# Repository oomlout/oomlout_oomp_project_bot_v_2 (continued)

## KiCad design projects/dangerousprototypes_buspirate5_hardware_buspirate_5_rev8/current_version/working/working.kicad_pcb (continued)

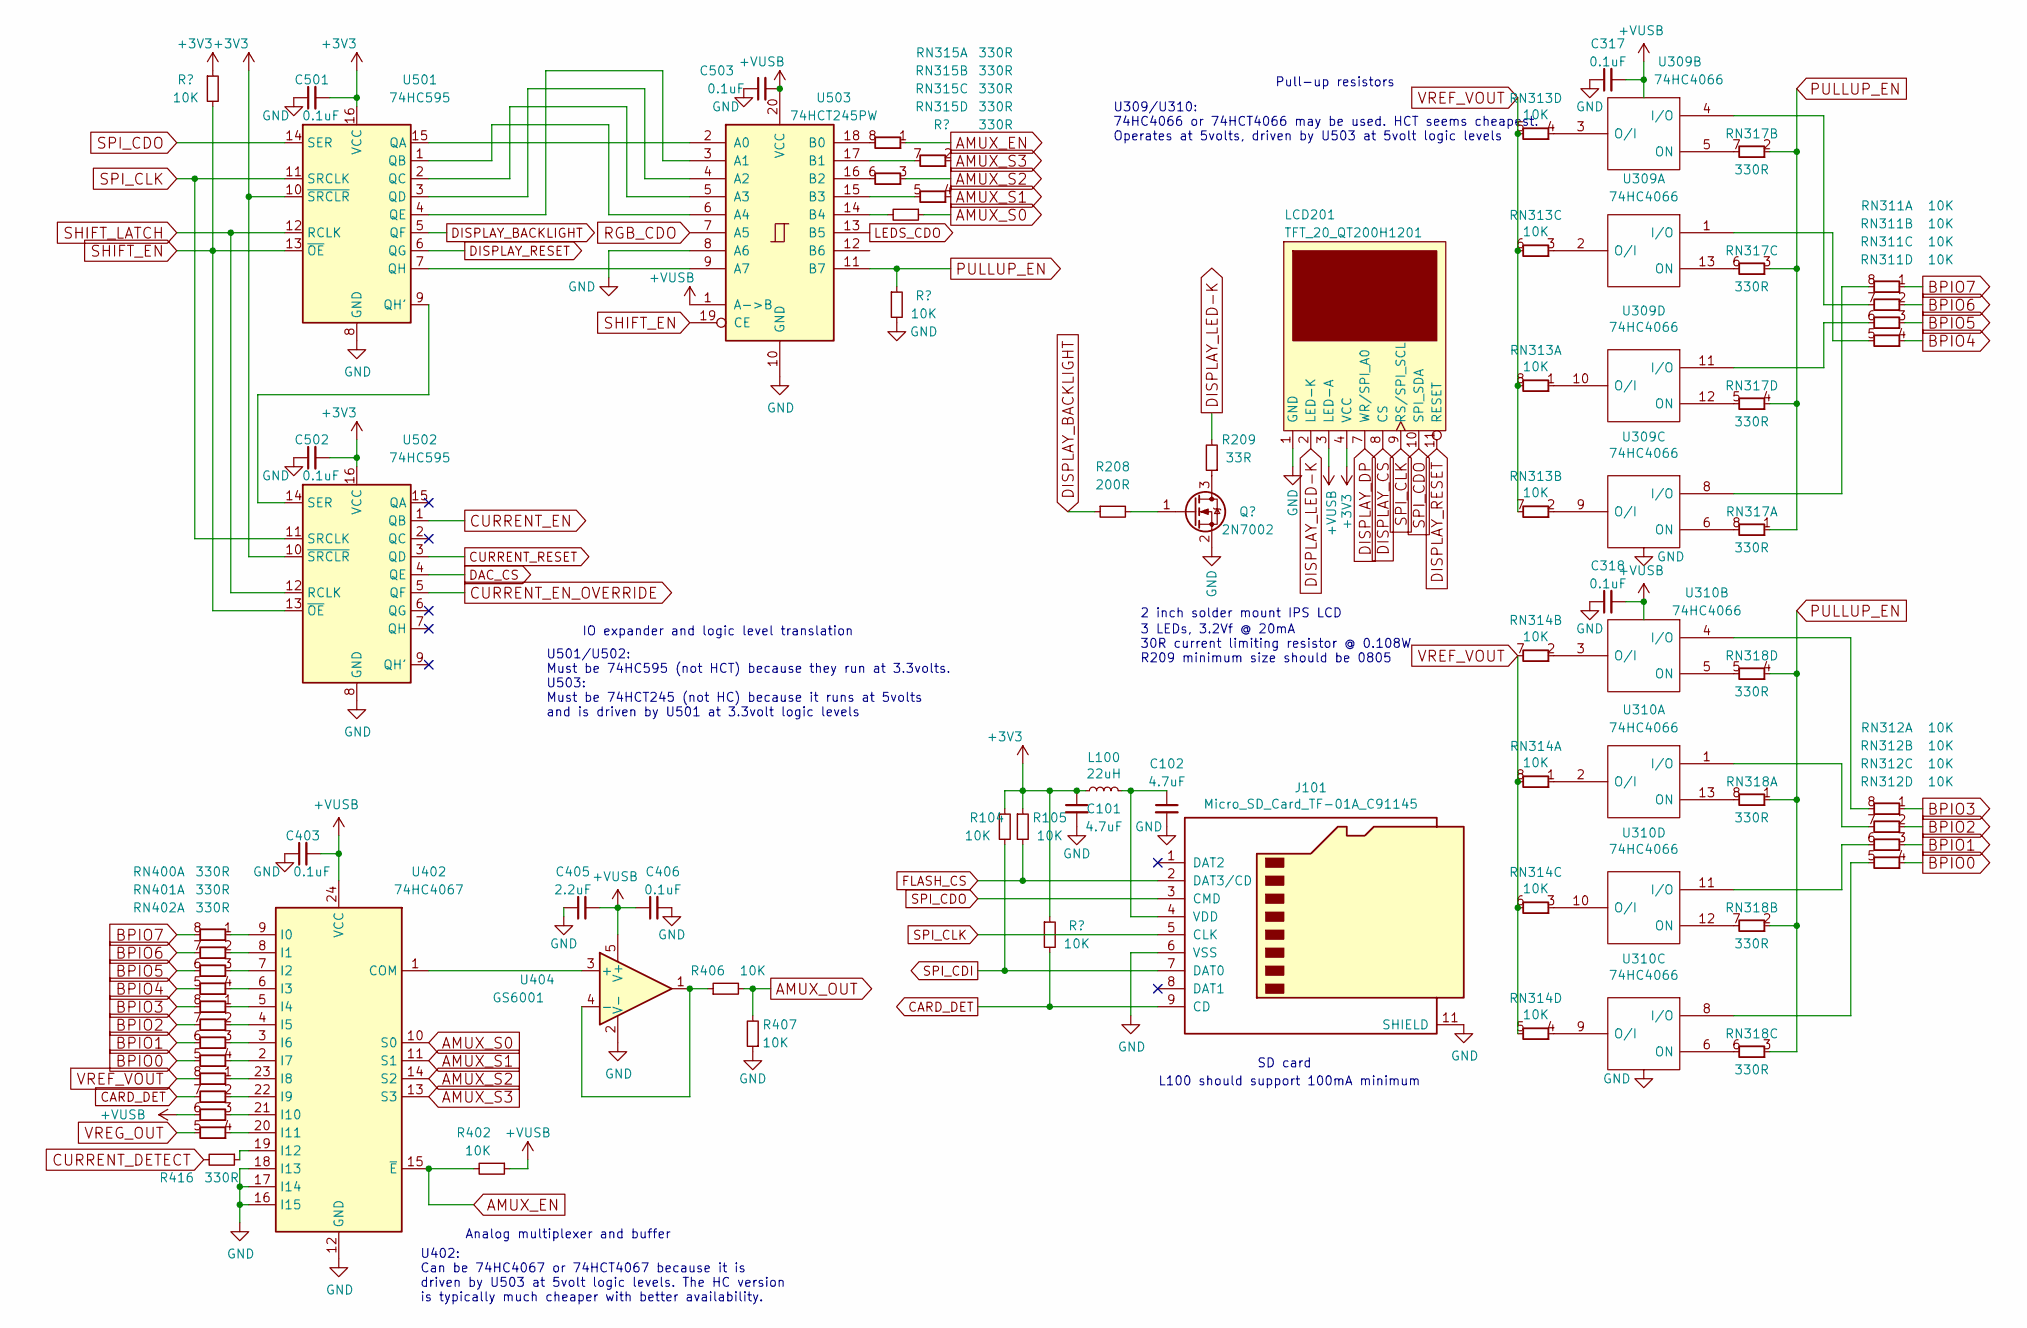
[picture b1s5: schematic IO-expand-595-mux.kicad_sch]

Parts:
C101, C102: 4.7uF; C_0402_1005Metric
C317, C318, C403, C406, C501, C502, C503: 0.1uF; C_0402_1005Metric
C405: 2.2uF; C_0402_1005Metric
J101: Micro_SD_Card_TF-01A_C91145; TF-01A_C91145
L100: 22uH; L_0603_1608Metric
LCD201: TFT_20_QT200H1201
Q202: 2N7002; SOT-23
R104, R105, R106, R312, R402, R406, R407, R501: 10K; R_0402_1005Metric
R208: 200R; R_0402_1005Metric
R209: 33R; R_0805_2012Metric
R316, R416: 330R; R_0402_1005Metric
RN311, RN312, RN313, RN314: 10K; R_Array_Convex_4x0402
RN315, RN317, RN318, RN400, RN401, RN402: 330R; R_Array_Convex_4x0402
U309, U310: 74HC4066; TSSOP-14_4.4x5mm_P0.65mm
U402: 74HC4067; TSSOP-24_4.4x7.8mm_P0.65mm
U404: GS6001; SOT-23-5
U501, U502: 74HC595; TSSOP-16_4.4x5mm_P0.65mm
U503: 74HCT245PW; TSSOP-20_4.4x6.5mm_P0.65mm

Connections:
+VUSB: C317.2, C318.2, C403.2, C405.2, C406.1, C503.2, LCD201.3 (LED-A), R402.1, RN402.6 (R1.8), U309.14 (Vdd), U310.14 (Vdd), U402.24 (VCC), U404.5 (V+), U503.1 (A->B), U503.20 (VCC); also elsewhere on the board
AMUX_EN: R402.2, RN315.1 (R1.1), U402.15 (~E)
AMUX_OUT: R406.2, R407.2; also elsewhere on the board
AMUX_S0: R316.1, U402.10 (S0)
AMUX_S1: RN315.4 (R1.1), U402.11 (S1)
AMUX_S2: RN315.3 (R1.1), U402.14 (S2)
AMUX_S3: RN315.2 (R1.1), U402.13 (S3)
BPIO0: RN312.4 (R1.1), RN401.5 (R1.8); also elsewhere on the board
BPIO1: RN312.3 (R1.1), RN401.6 (R1.8); also elsewhere on the board
BPIO2: RN312.2 (R1.1), RN401.7 (R1.8); also elsewhere on the board
BPIO3: RN312.1 (R1.1), RN401.8 (R1.8); also elsewhere on the board
BPIO4: RN311.4 (R1.1), RN400.5 (R1.8); also elsewhere on the board
BPIO5: RN311.3 (R1.1), RN400.6 (R1.8); also elsewhere on the board
BPIO6: RN311.2 (R1.1), RN400.7 (R1.8); also elsewhere on the board
BPIO7: RN311.1 (R1.1), RN400.8 (R1.8); also elsewhere on the board
CARD_DET: J101.9 (CD), R106.2, RN402.7 (R1.8)
CURRENT_DETECT: R416.2; also elsewhere on the board
CURRENT_EN: U502.1 (QB); also elsewhere on the board
CURRENT_EN_OVERRIDE: U502.5 (QF); also elsewhere on the board
CURRENT_RESET: U502.3 (QD); also elsewhere on the board
DAC_CS: U502.4 (QE)
DISPLAY_BACKLIGHT: R208.1, U501.5 (QF)
DISPLAY_CS: LCD201.8 (CS); also elsewhere on the board
DISPLAY_DP: LCD201.7 (WR/SPI_A0); also elsewhere on the board
DISPLAY_LED-K: LCD201.2 (LED-K), R209.2
DISPLAY_RESET: LCD201.11 (RESET), U501.6 (QG)
FLASH_CS: J101.2 (DAT3/CD), R105.2; also elsewhere on the board
GND: C101.2, C102.2, C317.1, C318.1, C403.1, C405.1, C406.2, C501.1, C502.1, C503.1, J101.6 (VSS), J101.11 (SHIELD), LCD201.1 (GND), LCD201.5 (GND), LCD201.6 (GND), LCD201.12 (GND), Q202.2 (S), R312.2, R407.1, U309.7 (Vss), U310.7 (Vss), U402.12 (GND), U402.16 (I15), U402.17 (I14), U402.18 (I13), U404.2 (V-), U501.8 (GND), U502.8 (GND), U503.8 (A6), U503.10 (GND); also elsewhere on the board
LEDS_CDO: U503.13 (B5); also elsewhere on the board
unnamed: C102.1, J101.4 (VDD), L100.2
unnamed: Q202.1 (G), R208.2
unnamed: Q202.3 (D), R209.1
unnamed: R316.2, U503.14 (B4)
unnamed: R406.1, U404.1, U404.4 (-)
unnamed: R416.1, U402.19 (I12)
unnamed: RN311.5 (R1.8), U309.1 (I/O)
unnamed: RN311.6 (R1.8), U309.11 (I/O)
unnamed: RN311.7 (R1.8), U309.4 (I/O)
unnamed: RN311.8 (R1.8), U309.8 (I/O)
unnamed: RN312.5 (R1.8), U310.8 (I/O)
unnamed: RN312.6 (R1.8), U310.11 (I/O)
unnamed: RN312.7 (R1.8), U310.1 (I/O)
unnamed: RN312.8 (R1.8), U310.4 (I/O)
unnamed: RN313.1 (R1.1), U309.10 (O/I)
unnamed: RN313.2 (R1.1), U309.9 (O/I)
unnamed: RN313.3 (R1.1), U309.2 (O/I)
unnamed: RN313.4 (R1.1), U309.3 (O/I)
unnamed: RN314.1 (R1.1), U310.2 (O/I)
unnamed: RN314.2 (R1.1), U310.3 (O/I)
unnamed: RN314.3 (R1.1), U310.10 (O/I)
unnamed: RN314.4 (R1.1), U310.9 (O/I)
unnamed: RN315.5 (R1.8), U503.15 (B3)
unnamed: RN315.6 (R1.8), U503.16 (B2)
unnamed: RN315.7 (R1.8), U503.17 (B1)
unnamed: RN315.8 (R1.8), U503.18 (B0)
unnamed: RN317.5 (R1.8), U309.12 (ON)
unnamed: RN317.6 (R1.8), U309.13 (ON)
unnamed: RN317.7 (R1.8), U309.5 (ON)
unnamed: RN317.8 (R1.8), U309.6 (ON)
unnamed: RN318.5 (R1.8), U310.5 (ON)
unnamed: RN318.6 (R1.8), U310.6 (ON)
unnamed: RN318.7 (R1.8), U310.12 (ON)
unnamed: RN318.8 (R1.8), U310.13 (ON)
unnamed: RN400.1 (R1.1), U402.9 (I0)
unnamed: RN400.2 (R1.1), U402.8 (I1)
unnamed: RN400.3 (R1.1), U402.7 (I2)
unnamed: RN400.4 (R1.1), U402.6 (I3)
unnamed: RN401.1 (R1.1), U402.5 (I4)
unnamed: RN401.2 (R1.1), U402.4 (I5)
unnamed: RN401.3 (R1.1), U402.3 (I6)
unnamed: RN401.4 (R1.1), U402.2 (I7)
unnamed: RN402.1 (R1.1), U402.23 (I8)
unnamed: RN402.2 (R1.1), U402.22 (I9)
unnamed: RN402.3 (R1.1), U402.21 (I10)
unnamed: RN402.4 (R1.1), U402.20 (I11)
unnamed: U402.1 (COM), U404.3 (+)
unnamed: U501.1 (QB), U503.6 (A4)
unnamed: U501.2 (QC), U503.5 (A3)
unnamed: U501.3 (QD), U503.4 (A2)
unnamed: U501.4 (QE), U503.3 (A1)
unnamed: U501.7 (QH), U503.9 (A7)
unnamed: U501.9 (QH'), U502.14 (SER)
unnamed: U501.15 (QA), U503.2 (A0)
PULLUP_EN: R312.1, RN317.1 (R1.1), RN317.2 (R1.1), RN317.3 (R1.1), RN317.4 (R1.1), RN318.1 (R1.1), RN318.2 (R1.1), RN318.3 (R1.1), RN318.4 (R1.1), U503.11 (B7)
RGB_CDO: U503.7 (A5); also elsewhere on the board
SHIFT_EN: R501.2, U501.13 (~OE), U502.13 (~OE), U503.19 (CE); also elsewhere on the board
SHIFT_LATCH: U501.12 (RCLK), U502.12 (RCLK); also elsewhere on the board
SPI_CDI: J101.7 (DAT0), R104.2; also elsewhere on the board
SPI_CDO: J101.3 (CMD), LCD201.10 (SPI_SDA), U501.14 (SER); also elsewhere on the board
SPI_CLK: J101.5 (CLK), LCD201.9 (RS/SPI_SCL), U501.11 (SRCLK), U502.11 (SRCLK); also elsewhere on the board
VREF_VOUT: RN313.5 (R1.8), RN313.6 (R1.8), RN313.7 (R1.8), RN313.8 (R1.8), RN314.5 (R1.8), RN314.6 (R1.8), RN314.7 (R1.8), RN314.8 (R1.8), RN402.8 (R1.8); also elsewhere on the board
VREG_OUT: RN402.5 (R1.8); also elsewhere on the board

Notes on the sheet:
3 LEDs, 3.2Vf @ 20mA 30R current limiting resistor @ 0.108W R209 minimum size should be 0805
2 inch solder mount IPS LCD
U402: Can be 74HC4067 or 74HCT4067 because it is driven by U503 at 5volt logic levels. The HC version is typically much cheaper with better availability.
SD card
Analog multiplexer and buffer
U501/U502: Must be 74HC595 (not HCT) because they run at 3.3volts. U503: Must be 74HCT245 (not HC) because it runs at 5volts and is driven by U501 at 3.3volt logic levels
U309/U310: 74HC4066 or 74HCT4066 may be used. HCT seems cheapest. Operates at 5volts, driven by U503 at 5volt logic levels
L100 should support 100mA minimum
IO expander and logic level translation
Pull-up resistors

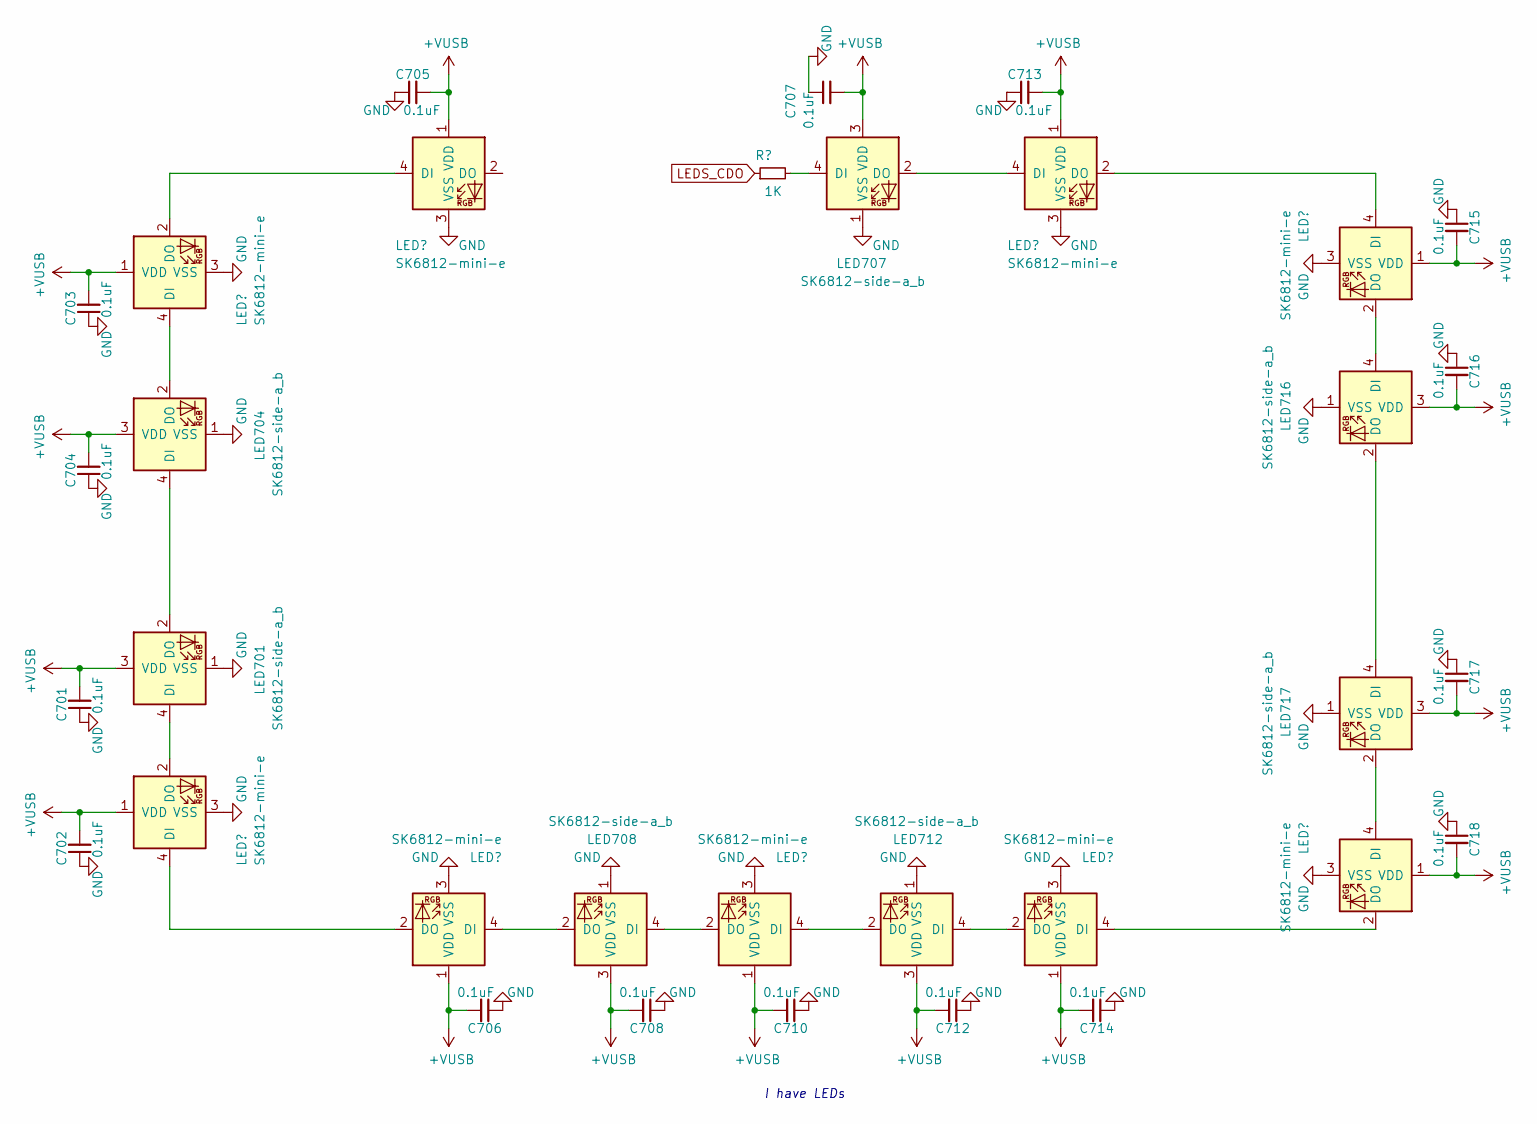
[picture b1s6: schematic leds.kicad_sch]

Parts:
C701, C702, C703, C704, C705, C706, C707, C708, C710, C712, C713, C714, C715, C716, C717, C718: 0.1uF; C_0402_1005Metric
LED701, LED704, LED707, LED708, LED712, LED716, LED717: SK6812-side-a_b
LED702, LED703, LED705, LED706, LED710, LED713, LED714, LED715, LED718: SK6812-mini-e
R502: 1K; R_0402_1005Metric

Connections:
+VUSB: C701.2, C702.2, C703.2, C704.2, C705.2, C706.2, C707.2, C708.2, C710.2, C712.2, C713.2, C714.2, C715.2, C716.2, C717.2, C718.2, LED701.3 (VDD), LED702.1 (VDD), LED703.1 (VDD), LED704.3 (VDD), LED705.1 (VDD), LED706.1 (VDD), LED707.3 (VDD), LED708.3 (VDD), LED710.1 (VDD), LED712.3 (VDD), LED713.1 (VDD), LED714.1 (VDD), LED715.1 (VDD), LED716.3 (VDD), LED717.3 (VDD), LED718.1 (VDD); also elsewhere on the board
GND: C701.1, C702.1, C703.1, C704.1, C705.1, C706.1, C707.1, C708.1, C710.1, C712.1, C713.1, C714.1, C715.1, C716.1, C717.1, C718.1, LED701.1 (VSS), LED702.3 (VSS), LED703.3 (VSS), LED704.1 (VSS), LED705.3 (VSS), LED706.3 (VSS), LED707.1 (VSS), LED708.1 (VSS), LED710.3 (VSS), LED712.1 (VSS), LED713.3 (VSS), LED714.3 (VSS), LED715.3 (VSS), LED716.1 (VSS), LED717.1 (VSS), LED718.3 (VSS); also elsewhere on the board
LEDS_CDO: R502.1; also elsewhere on the board
unnamed: LED701.2 (DO), LED704.4 (DI)
unnamed: LED701.4 (DI), LED702.2 (DO)
unnamed: LED702.4 (DI), LED706.2 (DO)
unnamed: LED703.2 (DO), LED705.4 (DI)
unnamed: LED703.4 (DI), LED704.2 (DO)
unnamed: LED706.4 (DI), LED708.2 (DO)
unnamed: LED707.2 (DO), LED713.4 (DI)
unnamed: LED707.4 (DI), R502.2
unnamed: LED708.4 (DI), LED710.2 (DO)
unnamed: LED710.4 (DI), LED712.2 (DO)
unnamed: LED712.4 (DI), LED714.2 (DO)
unnamed: LED713.2 (DO), LED715.4 (DI)
unnamed: LED714.4 (DI), LED718.2 (DO)
unnamed: LED715.2 (DO), LED716.4 (DI)
unnamed: LED716.2 (DO), LED717.4 (DI)
unnamed: LED717.2 (DO), LED718.4 (DI)

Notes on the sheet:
I have LEDs

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
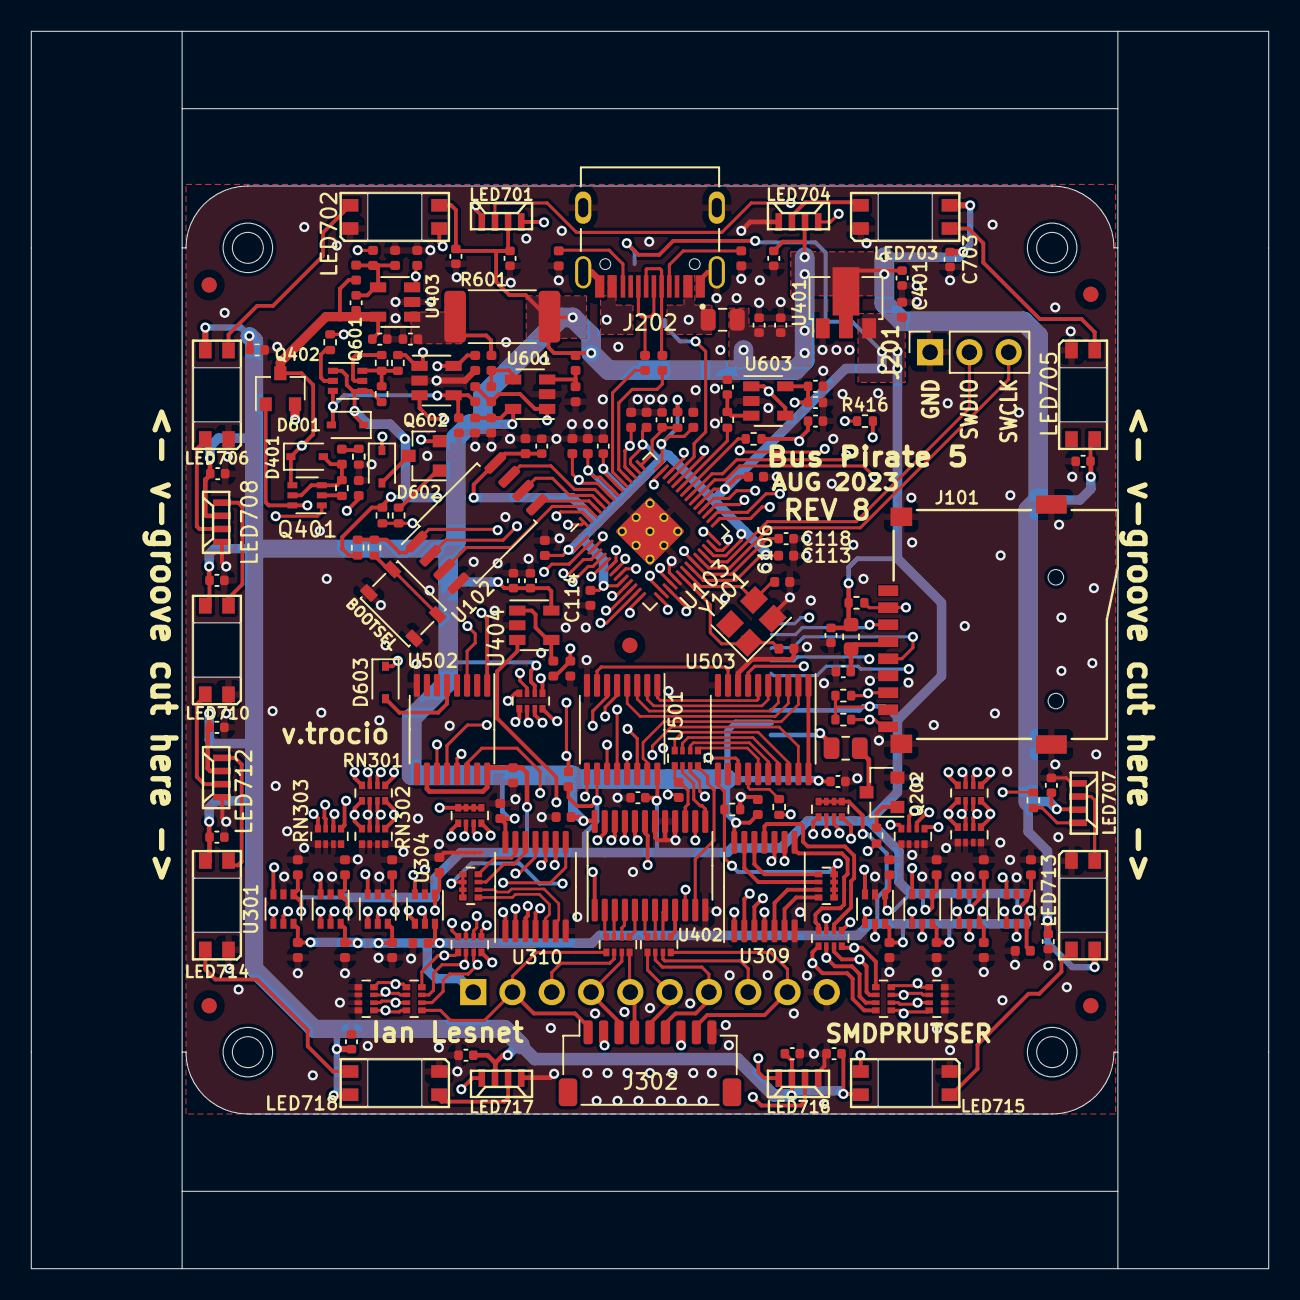
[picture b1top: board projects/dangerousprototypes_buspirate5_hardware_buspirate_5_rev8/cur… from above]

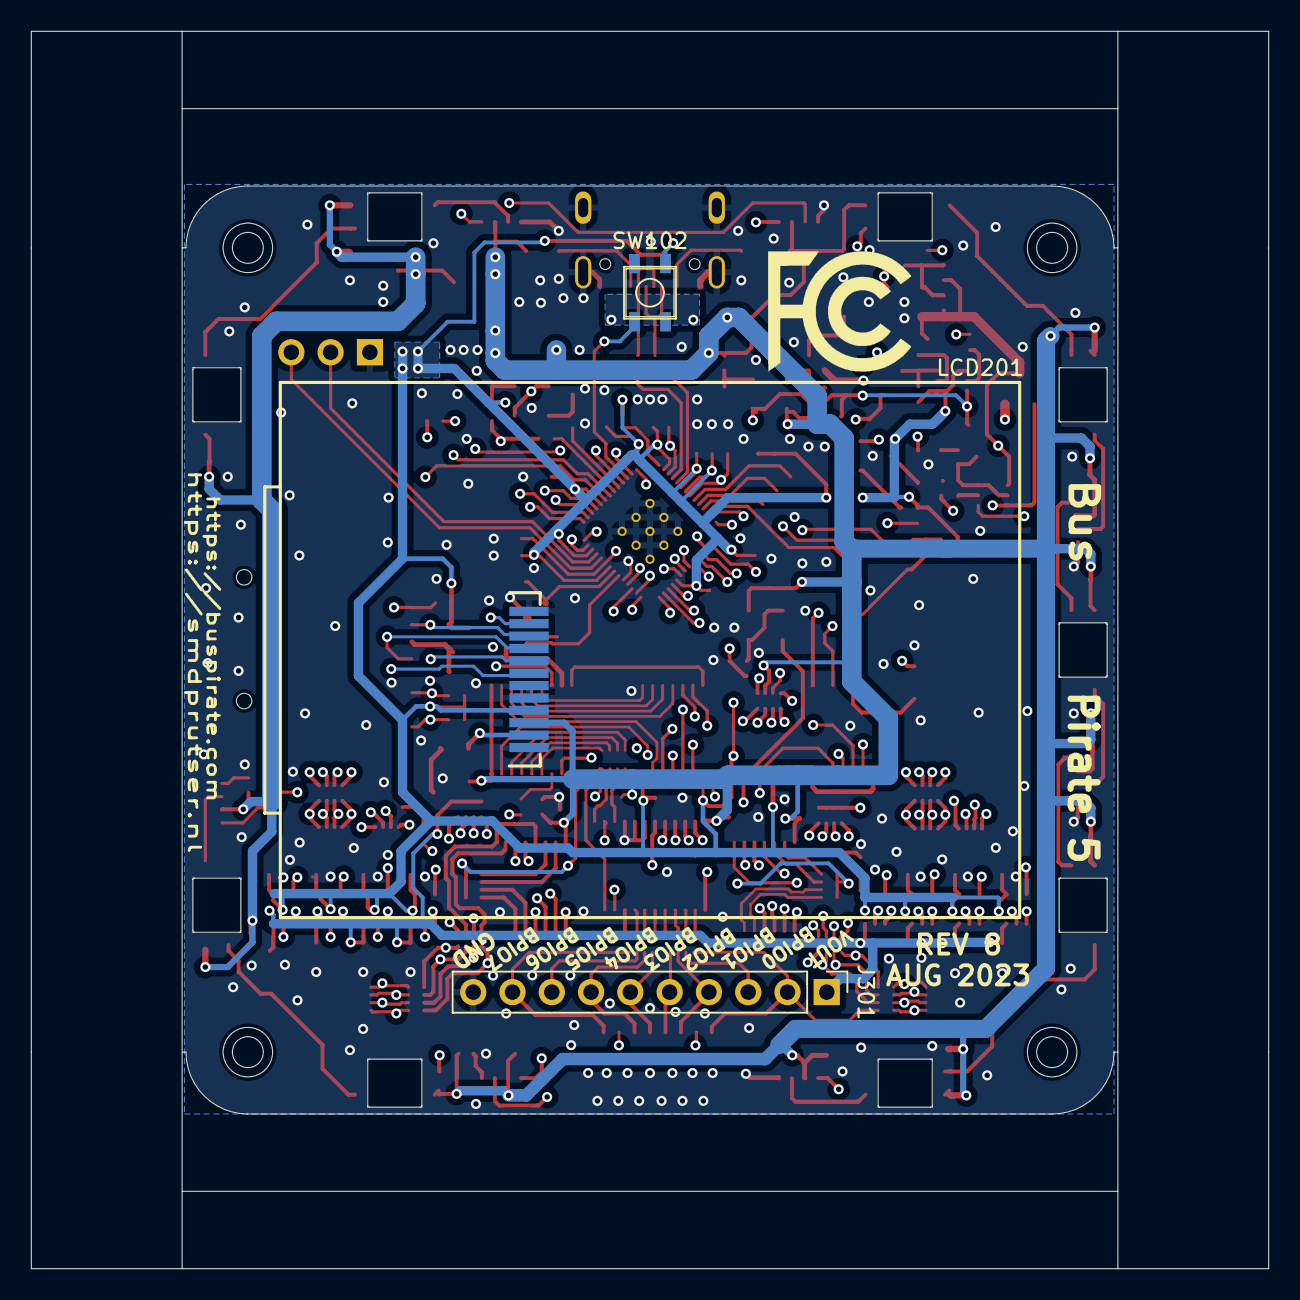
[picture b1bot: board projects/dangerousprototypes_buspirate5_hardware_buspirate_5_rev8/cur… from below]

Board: 4 copper layers, 80.0 x 80.0 mm, 203 parts (4 on the bottom side), 182 nets.

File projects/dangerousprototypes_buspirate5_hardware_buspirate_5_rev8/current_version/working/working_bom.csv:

"Id";"Designator";"Footprint";"Quantity";"Designation";"Supplier and ref";
1;"LED702,LED715,LED714,LED703,LED705,LED718,LED706,LED710,LED713";"SK6812-mini-e";9;"SK6812-mini-e";;;
2;"C402,C101,C202,C201,C401,C102,C404,C407";"C_0402_1005Metric";8;"4.7uF";;;
3;"C313,C308,C315,C304,C403,C314,C309,C112,C114,C110,C111,C113,C103,C118,C705,C708,C704,C706,C710,C712,C703,C701,C117,C501,C116,C715,C714,C716,C717,C718,C318,C502,C713,C406,C115,C707,C602,C605,C702,C311,C312,C503,C306,C307,C301,C302,C305,C303,C316,C317,C310,C414,C415,C416";"C_0402_1005Metric";54;"0.1uF";;;
4;"C107,C108,C109,C104,C405,C601,C413";"C_0402_1005Metric";7;"2.2uF";;;
5;"C106,C105";"C_0402_1005Metric";2;"15pF";;;
6;"U301,U304,U305,U307,U306,U303,U302,U308";"SOT-363_SC-70-6";8;"SN74LVC1T45DCK";;;
7;"R203,R202";"R_0402_1005Metric";2;"22R";;;
8;"R204,R201";"R_0402_1005Metric";2;"5.1K";;;
9;"L201";"L_0805_2012Metric";1;"1.5A";;;
10;"R407,R501,R402,R406,R104,R105,R410,R611,R609,R606,R610,R613,R106,R312,R414,R415";"R_0402_1005Metric";16;"10K";;;
11;"R103,R608,R612,R208";"R_0402_1005Metric";4;"200R";;;
12;"U103";"RP2040-QFN-56";1;"RP2040";;;
13;"U501,U502";"TSSOP-16_4.4x5mm_P0.65mm";2;"74HC595";;;
14;"RN302,RN307,RN304,RN310";"R_Array_Convex_4x0402";4;"1M";;;
15;"R209";"R_0805_2012Metric";1;"33R";;;
16;"U102";"SOP-8_5.28x5.23mm_P1.27mm";1;"W25Q128JVSIQ";;;
17;"U310,U309";"TSSOP-14_4.4x5mm_P0.65mm";2;"74HC4066";;;
18;"R101,R602,R603,R502";"R_0402_1005Metric";4;"1K";;;
19;"FID1,FID2,FID4,FID5,FID3";"Fiducial_1mm_Mask2mm";5;"Fiducial";;;
20;"J201";"PinSocket_1x03_P2.54mm_Vertical";1;"Conn_01x03";;;
21;"R102";"R_0402_1005Metric";1;"DNF";;;
22;"J302";"JST_SH_SM09B-SRSS-TB_1x09-1MP_P1.00mm_Horizontal";1;"Conn_01x09";;;
23;"U503";"TSSOP-20_4.4x6.5mm_P0.65mm";1;"74HCT245PW";;;
24;"Y101";"Crystal_SMD_3225-4Pin_3.2x2.5mm";1;"12Mhz";;;
25;"Q202";"SOT-23";1;"2N7002";;;
26;"L100";"L_0603_1608Metric";1;"22uH";;;
27;"J101";"TF-01A_C91145";1;"Micro_SD_Card_TF-01A_C91145";;;
28;"SW101";"SW_SPST_PTS810";1;"SW_SPST";;;
29;"D601,D401,D603,D602";"D_SOD-323";4;"1N4148WS";;;
30;"R405,R409,R408,R605,R604";"R_0402_1005Metric";5;"33K";;;
31;"R412,R401";"R_0402_1005Metric";2;"100K";;;
32;"R403";"R_0402_1005Metric";1;"102K";;;
33;"U601,U404,U603";"SOT-23-5";3;"GS6001";;;
34;"R601";"R_2512_6332Metric_Pad1.40x3.35mm_HandSolder";1;"0R2";;;
35;"C603";"C_0402_1005Metric";1;"DNF";;;
36;"U602";"SOT-23-5";1;"RS8901XF";;;
37;"Q402,Q602";"SOT-23";2;"WST3423";;;
38;"U403";"SOT-23-5";1;"AP2127";;;
39;"Q601";"SOT-363_SC-70-6";1;"MMDT3906";;;
40;"Q401";"SOT-363_SC-70-6";1;"BCM857";;;
41;"RN309,RN301,RN306,RN315,RN318,RN317,RN305,RN400,RN401,RN402";"R_Array_Convex_4x0402";10;"330R";;;
42;"U402";"TSSOP-24_4.4x7.8mm_P0.65mm";1;"74HC4067";;;
43;"RN303,RN308";"R_Array_Convex_4x0402";2;"100K";;;
44;"J202";"HRO_TYPE-C-31-M-12";1;"TYPE-C-31-M-12";;;
45;"RN313,RN314,RN312,RN311";"R_Array_Convex_4x0402";4;"10K";;;
46;"LED707,LED716,LED717,LED712,LED708,LED701,LED704";"SK6812-side-a_b";7;"SK6812-side-a_b";;;
47;"R316,R416";"R_0402_1005Metric";2;"330R";;;
48;"U401";"SOT-89-3";1;"ME6211A33PG-N";;;
49;"C408";"C_0402_1005Metric";1;"120pF";;;
50;"R404";"R_0402_1005Metric";1;"133K";;;
51;"J301";"PinHeader_1x10_P2.54mm_Vertical";1;"Conn_01x10";;;
52;"SW102";"GT-TC026X-HXXX-LX";1;"4P_button_sw";;;
53;"LCD201";"TFT_20_QT200H1201";1;"TFT_20_QT200H1201";;;
54;"logo1";"logo_fcc";1;"fcc_logo";;;

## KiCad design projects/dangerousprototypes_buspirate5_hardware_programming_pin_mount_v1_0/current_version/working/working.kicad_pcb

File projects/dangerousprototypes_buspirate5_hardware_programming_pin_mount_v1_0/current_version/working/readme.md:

# buspirate5_hardware
 
## summary 
* id: dangerousprototypes_buspirate5_hardware_programming_pin_mount_v1_0
* user: dangerousprototypes
* name: buspirate5_hardware
* board: programming_pin_mount_v1_0
* repo: https://github.com/DangerousPrototypes/BusPirate5-hardware
* src_file_repo_kicad_pcb: debug-station/programming_pin_mount.v1.0.kicad_pcb
* src_file_repo_kicad_pcb_link: https://github.com/DangerousPrototypes/BusPirate5-hardware/tree/main/debug-station/programming_pin_mount.v1.0.kicad_pcb

* src_file_repo_sch: debug-station/programming_pin_mount.v1.0.sch
* src_file_repo_sch_link: https://github.com/DangerousPrototypes/BusPirate5-hardware/tree/main/debug-station/programming_pin_mount.v1.0.sch
* full details link: https://github.com/oomlout/oomlout_oomp_project_bot_v_2/tree/main/projects/dangerousprototypes_buspirate5_hardware_programming_pin_mount_v1_0/current_version/working  

## schematic  
  
[schematic (pdf)](working_schematic.pdf) 

## pcb  

[board (pdf)](working.pdf)  

## working_bom
| Id | Designator | Footprint | Quantity | Designation | Supplier and ref |  | None | 
| --- | --- | --- | --- | --- | --- | --- | --- | 
| 1 | H1,H2,H3 | PinHeader_1x01_P1.00mm_Vertical | 3 | MountingHole_Pad |  |  | [''] | 
| 2 | J1 | PinHeader_1x03_P2.54mm_Horizontal | 1 | Conn_01x03 |  |  | [''] | 

## bom_schematic
| Ref | Qnty | Value | Cmp name | Footprint | Description | Vendor | DNP | 
| --- | --- | --- | --- | --- | --- | --- | --- | 
| H1, H2, H3 | 3 | MountingHole_Pad | MountingHole_Pad | Connector_PinHeader_1.00mm:PinHeader_1x01_P1.00mm_Vertical | Mounting Hole with connection |  |  | 
| H4, H5 | 2 | MountingHole | MountingHole | MountingHole:MountingHole_3.2mm_M3 | Mounting Hole without connection |  |  | 
| J1 | 1 | Conn_01x03 | Conn_01x03 | Connector_PinHeader_2.54mm:PinHeader_1x03_P2.54mm_Horizontal | Generic connector, single row, 01x03, script generated (kicad-library-utils/schlib/autogen/connector/) |  |  |

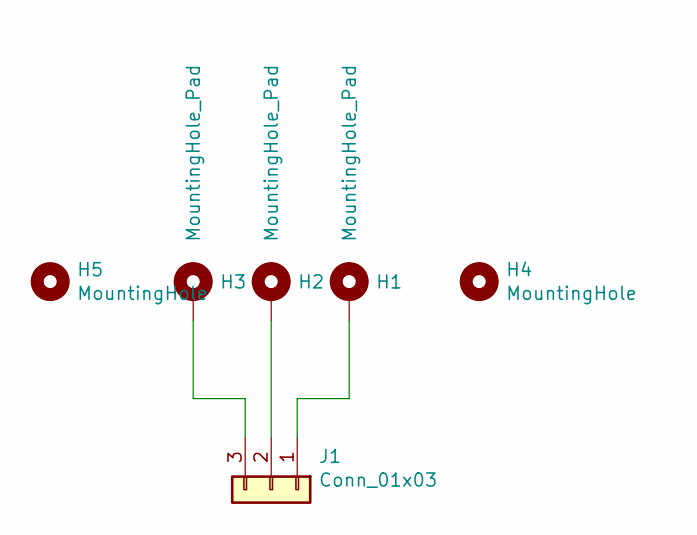
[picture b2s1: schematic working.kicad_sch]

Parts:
H1, H2, H3: MountingHole_Pad; PinHeader_1x01_P1.00mm_Vertical
H4, H5: MountingHole; MountingHole_3.2mm_M3
J1: Conn_01x03; PinHeader_1x03_P2.54mm_Horizontal

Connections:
unnamed: H1.1, J1.1
unnamed: H2.1, J1.2
unnamed: H3.1, J1.3

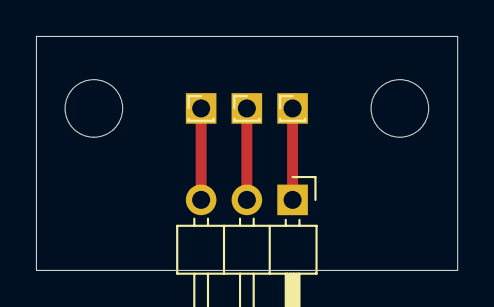
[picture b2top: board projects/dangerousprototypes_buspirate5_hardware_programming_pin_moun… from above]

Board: 2 copper layers, 23.4 x 13.0 mm, 6 parts (0 on the bottom side), 3 nets.

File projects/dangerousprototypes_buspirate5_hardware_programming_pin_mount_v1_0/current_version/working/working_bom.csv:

"Id";"Designator";"Footprint";"Quantity";"Designation";"Supplier and ref";
1;"H1,H2,H3";"PinHeader_1x01_P1.00mm_Vertical";3;"MountingHole_Pad";;;
2;"J1";"PinHeader_1x03_P2.54mm_Horizontal";1;"Conn_01x03";;;

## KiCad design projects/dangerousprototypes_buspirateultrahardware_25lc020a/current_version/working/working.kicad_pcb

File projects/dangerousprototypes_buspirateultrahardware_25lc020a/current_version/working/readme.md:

# buspirateultrahardware
 
## summary 
* id: dangerousprototypes_buspirateultrahardware_25lc020a
* user: dangerousprototypes
* name: buspirateultrahardware
* board: 25lc020a
* repo: https://github.com/DangerousPrototypes/BusPirateUltraHardware

* src_file_repo_sch: 
* src_file_repo_sch_link: https://github.com/DangerousPrototypes/BusPirateUltraHardware/tree/master/
* full details link: https://github.com/oomlout/oomlout_oomp_project_bot_v_2/tree/main/projects/dangerousprototypes_buspirateultrahardware_25lc020a/current_version/working  

## schematic  
  
[schematic (pdf)](working_schematic.pdf) 

## pcb  

[board (pdf)](working.pdf)  

## working_bom
| Id | Designator | Footprint | Quantity | Designation | Supplier and ref |  | None | 
| --- | --- | --- | --- | --- | --- | --- | --- | 
| 1 | R3,R2,R1 | R603 | 3 |  |  |  | [''] | 
| 2 | J1 | M1X10_FEMALE_RIGHT_ANGLED_PTH | 1 | CON_HEADER_1X10-RIGHT_ANGLED_PTH |  |  | [''] | 
| 3 | LED1 | LED-805 | 1 |  |  |  | [''] | 
| 4 | @HOLE0,@HOLE1 |  | 2 |  |  |  | [''] | 
| 5 | C1 | C603 | 1 |  |  |  | [''] | 
| 6 | J2 | M1X10 | 1 | CON_HEADER_1X10-PTH |  |  | [''] | 
| 7 | IC1 | SOIC127P600X175-8N | 1 | 25LC020A |  |  | [''] | 

## bom_schematic
| Ref | Qnty | Value | Cmp name | Footprint | Description | Vendor | DNP | 
| --- | --- | --- | --- | --- | --- | --- | --- | 
| C1 | 1 | CAPACITOR_NPOL-0603 | CAPACITOR_NPOL-0603 | working:C603 |  |  |  | 
| IC1 | 1 | 25LC020A-I_SN | 25LC020A-I_SN | working:SOIC127P600X175-8N |  |  |  | 
| J1 | 1 | CON_HEADER_1X10-RIGHT_ANGLED_PTH | CON_HEADER_1X10-RIGHT_ANGLED_PTH | working:M1X10_FEMALE_RIGHT_ANGLED_PTH |  |  |  | 
| J2 | 1 | CON_HEADER_1X10-PTH | CON_HEADER_1X10-PTH | working:M1X10 |  |  |  | 
| LED1 | 1 | LED-0805 | LED-0805 | working:LED-805 |  |  |  | 
| R1, R2, R3 | 3 | RESISTOR-0603 | RESISTOR-0603 | working:R603 |  |  |  |

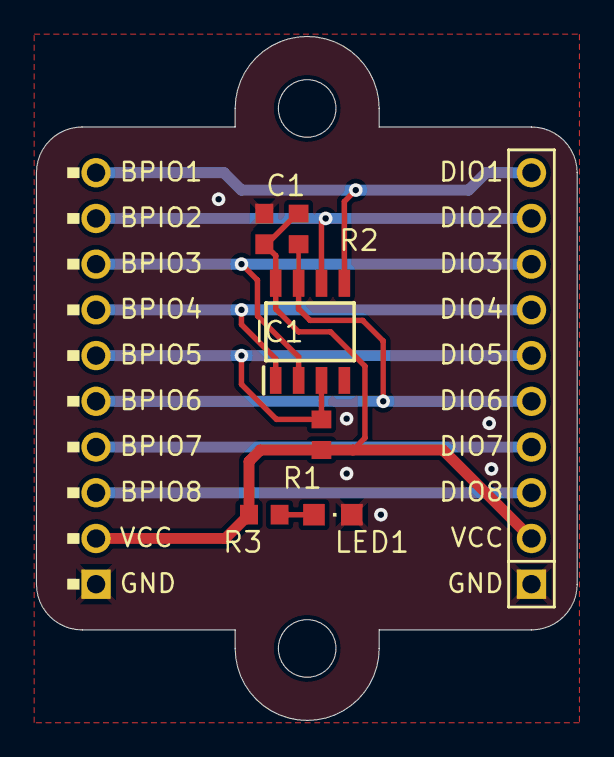
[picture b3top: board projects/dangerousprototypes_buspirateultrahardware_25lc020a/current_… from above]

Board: 2 copper layers, 30.0 x 38.0 mm, 10 parts (0 on the bottom side), 11 nets.

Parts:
@HOLE0, @HOLE1: (no value)
C1: C603
IC1: 25LC020A; SOIC127P600X175-8N
J1: CON_HEADER_1X10-RIGHT_ANGLED_PTH; M1X10_FEMALE_RIGHT_ANGLED_PTH
J2: CON_HEADER_1X10-PTH; M1X10
LED1: LED-805
R1, R2, R3: R603

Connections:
DIO1: IC1.5, J1.10, J2.10
DIO2: IC1.6, J1.9, J2.9
DIO3: IC1.2, J1.8, J2.8
DIO4: IC1.1, J1.7, J2.7
DIO5: IC1.3, J1.6, J2.6, R1.1
DIO6: IC1.7, J1.5, J2.5, R2.1
DIO7: J1.4, J2.4
DIO8: J1.3, J2.3
GND: C1.2, IC1.4, J1.1, J2.1, LED1.C
unnamed: LED1.A, R3.1
VCC: C1.1, IC1.8, J1.2, J2.2, R1.2, R2.2, R3.2

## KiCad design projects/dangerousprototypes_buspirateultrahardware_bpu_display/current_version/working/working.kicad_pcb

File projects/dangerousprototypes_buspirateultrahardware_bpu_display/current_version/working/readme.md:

# buspirateultrahardware
 
## summary 
* id: dangerousprototypes_buspirateultrahardware_bpu_display
* user: dangerousprototypes
* name: buspirateultrahardware
* board: bpu_display
* repo: https://github.com/DangerousPrototypes/BusPirateUltraHardware

* src_file_repo_sch: 
* src_file_repo_sch_link: https://github.com/DangerousPrototypes/BusPirateUltraHardware/tree/master/
* full details link: https://github.com/oomlout/oomlout_oomp_project_bot_v_2/tree/main/projects/dangerousprototypes_buspirateultrahardware_bpu_display/current_version/working  

## schematic  
  
[schematic (pdf)](working_schematic.pdf) 

## pcb  

[board (pdf)](working.pdf)  

## working_bom
| Id | Designator | Footprint | Quantity | Designation | Supplier and ref |  | None | 
| --- | --- | --- | --- | --- | --- | --- | --- | 
| 1 | DISP1 | HT020SQV003NS_QT020HLCG00 | 1 | DISP_TFT20_HT020SQV003NS_QT020HLCG00 |  |  | [''] | 
| 2 | @HOLE1,@HOLE3,@HOLE2,@HOLE0 |  | 4 |  |  |  | [''] | 
| 3 | PAGE1 | DP_LOGO | 1 | FRAME_DINA4_L |  |  | [''] | 
| 4 | J1 | X05B20L10T | 1 | CON-FPC_X05B20L10T |  |  | [''] | 
| 5 | R2 | R0603 | 1 | 10R |  |  | [''] | 
| 6 | R1 | R0603 | 1 | 10K |  |  | [''] | 
| 7 | Q1 | SOT-23 | 1 | MMBF170 |  |  | [''] | 

## bom_schematic
| Ref | Qnty | Value | Cmp name | Footprint | Description | Vendor | DNP | 
| --- | --- | --- | --- | --- | --- | --- | --- | 
| DISP1 | 1 | DISP_TFT20_HT020SQV003NS_QT020HLCG00 | DISP_TFT20_HT020SQV003NS_QT020HLCG00 | working:HT020SQV003NS_QT020HLCG00 |  |  |  | 
| J1 | 1 | CON-FPC_X05B20L10T | CON-FPC_X05B20L10T | working:X05B20L10T |  |  |  | 
| PAGE1 | 1 | FRAME_DINA4_L | FRAME_DINA4_L | working:DP_LOGO |  |  |  | 
| Q1 | 1 | MMBF170 | TRANSISTOR_FET_BS170-SOT-23 | working:SOT-23 |  |  |  | 
| R1 | 1 | 10K | R-EU_R0603 | working:R0603 |  |  |  | 
| R2 | 1 | 10R | R-EU_R0603 | working:R0603 |  |  |  |

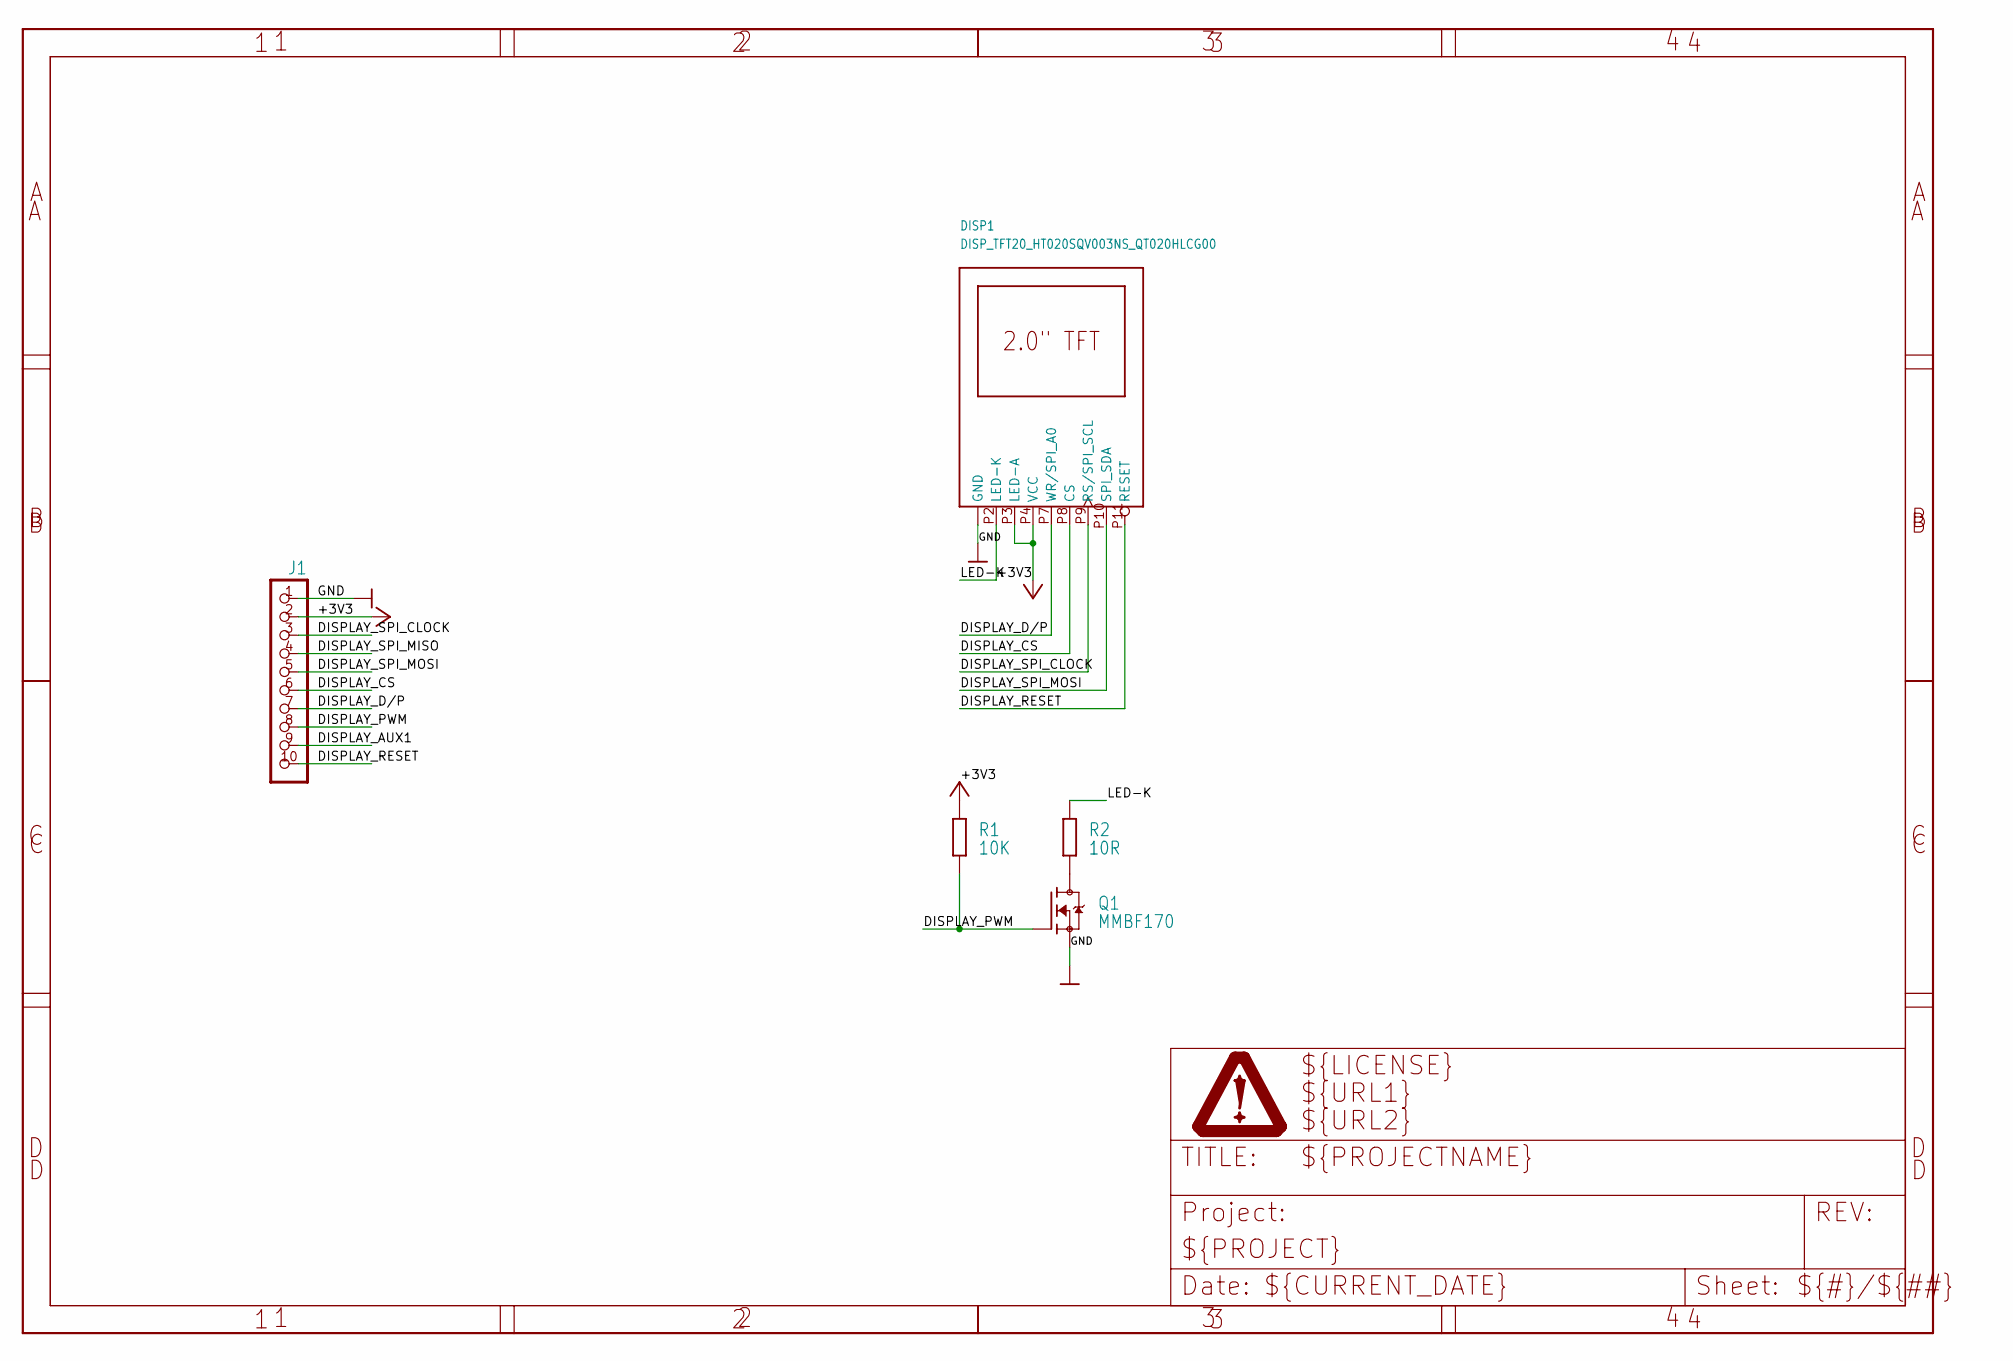
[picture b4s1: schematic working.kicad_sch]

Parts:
DISP1: DISP_TFT20_HT020SQV003NS_QT020HLCG00; HT020SQV003NS_QT020HLCG00
J1: CON-FPC_X05B20L10T; X05B20L10T
PAGE1: FRAME_DINA4_L; DP_LOGO
Q1: MMBF170; SOT-23
R1: 10K; R0603
R2: 10R; R0603

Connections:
+3V3: DISP1.P3 (LED-A), DISP1.P4 (VCC), J1.2, R1.2
DISPLAY_AUX1: J1.9
DISPLAY_CS: DISP1.P8 (CS), J1.6
DISPLAY_D/P: DISP1.P7 (WR/SPI_A0), J1.7
DISPLAY_PWM: J1.8, Q1.1 (G), R1.1
DISPLAY_RESET: DISP1.P11 (RESET), J1.10
DISPLAY_SPI_CLOCK: DISP1.P9 (RS/SPI_SCL), J1.3
DISPLAY_SPI_MISO: J1.4
DISPLAY_SPI_MOSI: DISP1.P10 (SPI_SDA), J1.5
GND: DISP1.P1 (GND), DISP1.P5 (GND), DISP1.P6 (GND), DISP1.P12 (GND), J1.1, Q1.2 (S)
LED-K: DISP1.P2 (LED-K), R2.2
unnamed: Q1.3 (D), R2.1
